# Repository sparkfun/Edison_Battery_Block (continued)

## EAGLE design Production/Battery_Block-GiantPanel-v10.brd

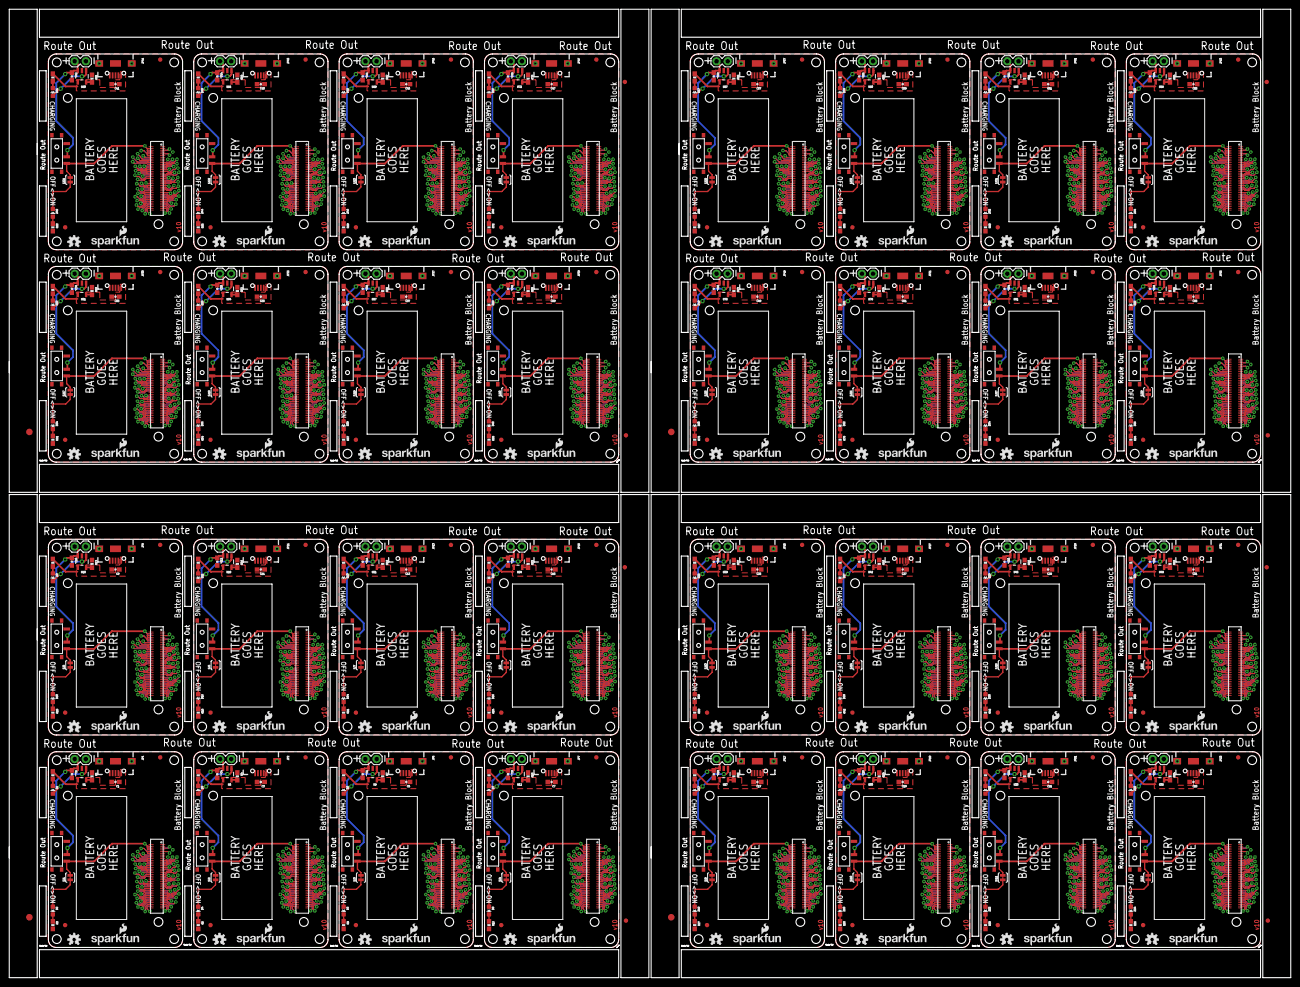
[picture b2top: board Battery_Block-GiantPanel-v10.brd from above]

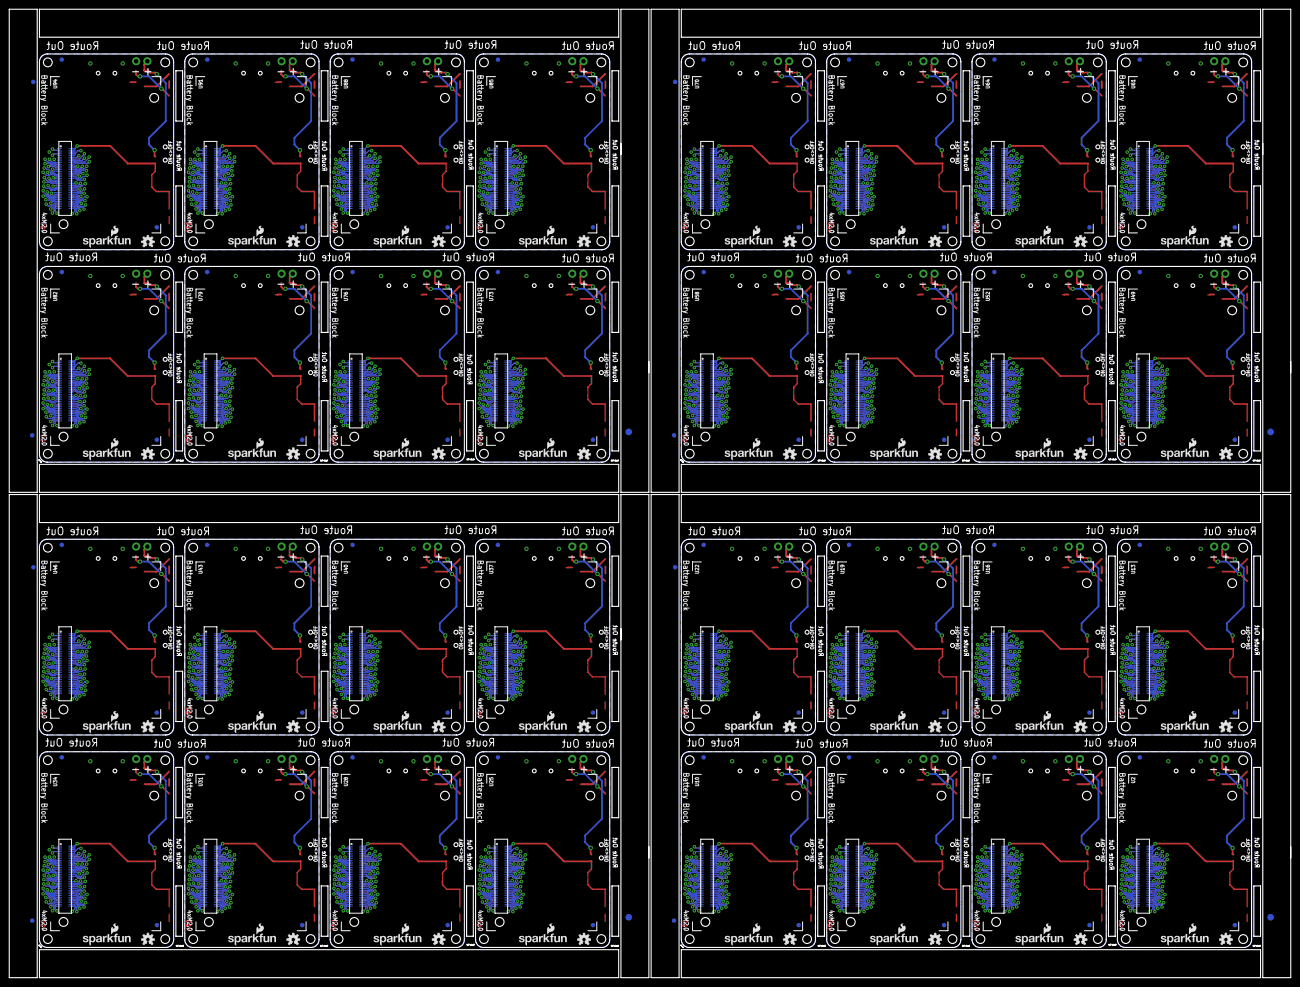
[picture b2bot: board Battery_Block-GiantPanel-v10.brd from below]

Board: 2 copper layers, 291.1 x 220.0 mm, 728 parts (204 on the bottom side), 2080 nets.

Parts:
C1, C2, C3, C4, C5, C6, C7, C8, C9, C10, C11, C12, C13, C14, C15, C16, C17, C18, C19, C20, C21, C22, C23, C24, C25, C26, C27, C28, C29, C30, C31, C32, C33, C34, C35, C36, C37, C38, C39, C40, C41, C42, C43, C44, C45, C46, C47, C48, C49, C50, C51, C52, C53, C54, C55, C56, C57, C58, C59, C60, C61, C62, C63, C64: 4.7uF; 0603-CAP
D1, D3, D5, D7, D9, D11, D13, D15, D17, D19, D21, D23, D25, D27, D29, D31, D33, D35, D37, D39, D41, D43, D45, D47, D49, D51, D53, D55, D57, D59, D61, D63: RED; LED-0603
D2, D4, D6, D8, D10, D12, D14, D16, D18, D20, D22, D24, D26, D28, D30, D32, D34, D36, D38, D40, D42, D44, D46, D48, D50, D52, D54, D56, D58, D60, D62, D64: BLUE; LED-0603
E$1, E$2, E$9, E$10, E$15, E$16, E$21, E$22: FIDUCIAL-1.5X3
E$3, E$4, E$5, E$6, E$7, E$8, E$11, E$12, E$13, E$14, E$17, E$18, E$19, E$20, E$23, E$24: FIDUCIAL-1X2
FID1, FID2, FID3, FID4, FID5, FID6, FID7, FID8, FID9, FID10, FID11, FID12, FID13, FID14, FID15, FID16, FID17, FID18, FID19, FID20, FID21, FID22, FID23, FID24, FID25, FID26, FID27, FID28, FID29, FID30, FID31, FID32, FID33, FID34, FID35, FID36, FID37, FID38, FID39, FID40, FID41, FID42, FID43, FID44, FID45, FID46, FID47, FID48, FID49, FID50, FID51, FID52, FID53, FID54, FID55, FID56, FID57, FID58, FID59, FID60, FID61, FID62, FID63, FID64, FID65, FID66, FID67, FID68, FID69, FID70, FID71, FID72, FID73, FID74, FID75, FID76, FID77, FID78, FID79, FID80, FID81, FID82, FID83, FID84, FID85, FID86, FID87, FID88, FID89, FID90, FID91, FID92, FID93, FID94, FID95, FID96, FID97, FID98, FID99, FID100, FID101, FID102, FID103, FID104, FID105, FID106, FID107, FID108, FID109, FID110, FID111, FID112, FID113, FID114, FID115, FID116, FID117, FID118, FID119, FID120, FID121, FID122, FID123, FID124, FID125, FID126, FID127, FID128: FIDUCIAL1X2; FIDUCIAL-1X2
JP1, JP2, JP5, JP7, JP9, JP11, JP13, JP15, JP17, JP19, JP21, JP23, JP25, JP27, JP29, JP31, JP33, JP35, JP37, JP39, JP41, JP43, JP45, JP47, JP49, JP51, JP53, JP55, JP57, JP59, JP61, JP63: USB_MICROB_PLUG; USB-B-MICRO-SMD_V03
JP3, JP4, JP6, JP8, JP10, JP12, JP14, JP16, JP18, JP20, JP22, JP24, JP26, JP28, JP30, JP32, JP34, JP36, JP38, JP40, JP42, JP44, JP46, JP48, JP50, JP52, JP54, JP56, JP58, JP60, JP62, JP64: M02PTH; 1X02
LOGO1, LOGO2, LOGO5, LOGO7, LOGO9, LOGO11, LOGO13, LOGO15, LOGO17, LOGO19, LOGO21, LOGO23, LOGO25, LOGO27, LOGO29, LOGO31, LOGO33, LOGO35, LOGO37, LOGO39, LOGO41, LOGO43, LOGO45, LOGO47, LOGO49, LOGO51, LOGO53, LOGO55, LOGO57, LOGO59, LOGO61, LOGO63, LOGO65, LOGO67, LOGO69, LOGO71, LOGO73, LOGO75, LOGO77, LOGO79, LOGO81, LOGO83, LOGO85, LOGO87, LOGO89, LOGO91, LOGO93, LOGO95, LOGO97, LOGO99, LOGO101, LOGO103, LOGO105, LOGO107, LOGO109, LOGO111, LOGO113, LOGO115, LOGO117, LOGO119, LOGO121, LOGO123, LOGO125, LOGO127: OSHW-LOGOS; OSHW-LOGO-S
LOGO3, LOGO4, LOGO6, LOGO8, LOGO10, LOGO12, LOGO14, LOGO16, LOGO18, LOGO20, LOGO22, LOGO24, LOGO26, LOGO28, LOGO30, LOGO32, LOGO34, LOGO36, LOGO38, LOGO40, LOGO42, LOGO44, LOGO46, LOGO48, LOGO50, LOGO52, LOGO54, LOGO56, LOGO58, LOGO60, LOGO62, LOGO64, LOGO66, LOGO68, LOGO70, LOGO72, LOGO74, LOGO76, LOGO78, LOGO80, LOGO82, LOGO84, LOGO86, LOGO88, LOGO90, LOGO92, LOGO94, LOGO96, LOGO98, LOGO100, LOGO102, LOGO104, LOGO106, LOGO108, LOGO110, LOGO112, LOGO114, LOGO116, LOGO118, LOGO120, LOGO122, LOGO124, LOGO126, LOGO128: SFE_LOGO_NAME_FLAME.1_INCH; SFE_LOGO_NAME_FLAME_.1
R1, R4, R7, R10, R13, R16, R19, R22, R25, R28, R31, R34, R37, R40, R43, R46, R49, R52, R55, R58, R61, R64, R67, R70, R73, R76, R79, R82, R85, R88, R91, R94: 2.0k; 0603-RES
R2, R5, R8, R11, R14, R17, R20, R23, R26, R29, R32, R35, R38, R41, R44, R47, R50, R53, R56, R59, R62, R65, R68, R71, R74, R77, R80, R83, R86, R89, R92, R95: 330; 0603-RES
R3, R6, R9, R12, R15, R18, R21, R24, R27, R30, R33, R36, R39, R42, R45, R48, R51, R54, R57, R60, R63, R66, R69, R72, R75, R78, R81, R84, R87, R90, R93, R96: 1k; 0603-RES
SJ1, SJ2, SJ3, SJ4, SJ5, SJ6, SJ7, SJ8, SJ9, SJ10, SJ11, SJ12, SJ13, SJ14, SJ15, SJ16, SJ17, SJ18, SJ19, SJ20, SJ21, SJ22, SJ23, SJ24, SJ25, SJ26, SJ27, SJ28, SJ29, SJ30, SJ31, SJ32: LED DISABLE; PAD-JUMPER-2-NC_BY_TRACE_YES_SILK
SW1, SW2, SW3, SW4, SW5, SW6, SW7, SW8, SW9, SW10, SW11, SW12, SW13, SW14, SW15, SW16, SW17, SW18, SW19, SW20, SW21, SW22, SW23, SW24, SW25, SW26, SW27, SW28, SW29, SW30, SW31, SW32: SWITCH_SPDT; KPS-1290
U1, U6, U9, U12, U15, U18, U21, U24, U27, U30, U33, U36, U39, U42, U45, U48, U51, U54, U57, U60, U63, U66, U69, U72, U75, U78, U81, U84, U87, U90, U93, U96: MCP73831; SOT23-5
U2, U4, U7, U10, U13, U16, U19, U22, U25, U28, U31, U34, U37, U40, U43, U46, U49, U52, U55, U58, U61, U64, U67, U70, U73, U76, U79, U82, U85, U88, U91, U94: EDISON_CONNECTOR_FULLMOUNTING_HOLES; EDISON_DAUGHTER
U3, U5, U8, U11, U14, U17, U20, U23, U26, U29, U32, U35, U38, U41, U44, U47, U50, U53, U56, U59, U62, U65, U68, U71, U74, U77, U80, U83, U86, U89, U92, U95: EDISON_CONNECTOR_FULLHEADER; DF40C-70DP-0.4(51)

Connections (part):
1.8V: U2.12, U3.12
1.8V1: U4.12, U5.12
1.8V2: U7.12, U8.12
1.8V3: U10.12, U11.12
1.8V4: U13.12, U14.12
1.8V5: U16.12, U17.12
1.8V6: U19.12, U20.12
1.8V7: U22.12, U23.12
1.8V8: U25.12, U26.12
1.8V9: U28.12, U29.12
1.8V10: U31.12, U32.12
1.8V11: U34.12, U35.12
1.8V12: U37.12, U38.12
1.8V13: U40.12, U41.12
1.8V14: U43.12, U44.12
1.8V15: U46.12, U47.12
1.8V16: U49.12, U50.12
1.8V17: U52.12, U53.12
1.8V18: U55.12, U56.12
1.8V19: U58.12, U59.12
1.8V20: U61.12, U62.12
1.8V21: U64.12, U65.12
1.8V22: U67.12, U68.12
1.8V23: U70.12, U71.12
1.8V24: U73.12, U74.12
1.8V25: U76.12, U77.12
1.8V26: U79.12, U80.12
1.8V27: U82.12, U83.12
1.8V28: U85.12, U86.12
1.8V29: U88.12, U89.12
1.8V30: U91.12, U92.12
1.8V31: U94.12, U95.12
3.3V: U2.8, U2.10, U3.8, U3.10
3.3V1: U4.8, U4.10, U5.8, U5.10
3.3V2: U7.8, U7.10, U8.8, U8.10
3.3V3: U10.8, U10.10, U11.8, U11.10
3.3V4: U13.8, U13.10, U14.8, U14.10
3.3V5: U16.8, U16.10, U17.8, U17.10
3.3V6: U19.8, U19.10, U20.8, U20.10
3.3V7: U22.8, U22.10, U23.8, U23.10
3.3V8: U25.8, U25.10, U26.8, U26.10
3.3V9: U28.8, U28.10, U29.8, U29.10
3.3V10: U31.8, U31.10, U32.8, U32.10
3.3V11: U34.8, U34.10, U35.8, U35.10
3.3V12: U37.8, U37.10, U38.8, U38.10
3.3V13: U40.8, U40.10, U41.8, U41.10
3.3V14: U43.8, U43.10, U44.8, U44.10
3.3V15: U46.8, U46.10, U47.8, U47.10
3.3V16: U49.8, U49.10, U50.8, U50.10
3.3V17: U52.8, U52.10, U53.8, U53.10
3.3V18: U55.8, U55.10, U56.8, U56.10
3.3V19: U58.8, U58.10, U59.8, U59.10
3.3V20: U61.8, U61.10, U62.8, U62.10
3.3V21: U64.8, U64.10, U65.8, U65.10
3.3V22: U67.8, U67.10, U68.8, U68.10
3.3V23: U70.8, U70.10, U71.8, U71.10
3.3V24: U73.8, U73.10, U74.8, U74.10
3.3V25: U76.8, U76.10, U77.8, U77.10
3.3V26: U79.8, U79.10, U80.8, U80.10
3.3V27: U82.8, U82.10, U83.8, U83.10
3.3V28: U85.8, U85.10, U86.8, U86.10
3.3V29: U88.8, U88.10, U89.8, U89.10
3.3V30: U91.8, U91.10, U92.8, U92.10
3.3V31: U94.8, U94.10, U95.8, U95.10
DCIN: U2.14, U3.14
DCIN1: U4.14, U5.14
DCIN2: U7.14, U8.14
DCIN3: U10.14, U11.14
DCIN4: U13.14, U14.14
DCIN5: U16.14, U17.14
DCIN6: U19.14, U20.14
DCIN7: U22.14, U23.14
DCIN8: U25.14, U26.14
DCIN9: U28.14, U29.14
DCIN10: U31.14, U32.14
DCIN11: U34.14, U35.14
DCIN12: U37.14, U38.14
DCIN13: U40.14, U41.14
DCIN14: U43.14, U44.14
DCIN15: U46.14, U47.14
DCIN16: U49.14, U50.14
DCIN17: U52.14, U53.14
DCIN18: U55.14, U56.14
DCIN19: U58.14, U59.14
DCIN20: U61.14, U62.14
DCIN21: U64.14, U65.14
DCIN22: U67.14, U68.14
DCIN23: U70.14, U71.14
DCIN24: U73.14, U74.14
DCIN25: U76.14, U77.14
DCIN26: U79.14, U80.14
DCIN27: U82.14, U83.14
DCIN28: U85.14, U86.14
DCIN29: U88.14, U89.14
DCIN30: U91.14, U92.14
DCIN31: U94.14, U95.14
FAULT: U2.19, U3.19
FAULT1: U4.19, U5.19
FAULT2: U7.19, U8.19
FAULT3: U10.19, U11.19
FAULT4: U13.19, U14.19
FAULT5: U16.19, U17.19
FAULT6: U19.19, U20.19
FAULT7: U22.19, U23.19
FAULT8: U25.19, U26.19
FAULT9: U28.19, U29.19
FAULT10: U31.19, U32.19
FAULT11: U34.19, U35.19
FAULT12: U37.19, U38.19
FAULT13: U40.19, U41.19
FAULT14: U43.19, U44.19
FAULT15: U46.19, U47.19
FAULT16: U49.19, U50.19
FAULT17: U52.19, U53.19
FAULT18: U55.19, U56.19
FAULT19: U58.19, U59.19
FAULT20: U61.19, U62.19
FAULT21: U64.19, U65.19
FAULT22: U67.19, U68.19
FAULT23: U70.19, U71.19
FAULT24: U73.19, U74.19
FAULT25: U76.19, U77.19
FAULT26: U79.19, U80.19
FAULT27: U82.19, U83.19
FAULT28: U85.19, U86.19
FAULT29: U88.19, U89.19
FAULT30: U91.19, U92.19
FAULT31: U94.19, U95.19
FW_RCVR: U2.69, U3.69
FW_RCVR1: U4.69, U5.69
FW_RCVR2: U7.69, U8.69
FW_RCVR3: U10.69, U11.69
FW_RCVR4: U13.69, U14.69
FW_RCVR5: U16.69, U17.69
FW_RCVR6: U19.69, U20.69
FW_RCVR7: U22.69, U23.69
FW_RCVR8: U25.69, U26.69
FW_RCVR9: U28.69, U29.69
FW_RCVR10: U31.69, U32.69
FW_RCVR11: U34.69, U35.69
FW_RCVR12: U37.69, U38.69
FW_RCVR13: U40.69, U41.69
FW_RCVR14: U43.69, U44.69
FW_RCVR15: U46.69, U47.69
FW_RCVR16: U49.69, U50.69
FW_RCVR17: U52.69, U53.69
FW_RCVR18: U55.69, U56.69
FW_RCVR19: U58.69, U59.69
FW_RCVR20: U61.69, U62.69
FW_RCVR21: U64.69, U65.69
FW_RCVR22: U67.69, U68.69
FW_RCVR23: U70.69, U71.69
FW_RCVR24: U73.69, U74.69
FW_RCVR25: U76.69, U77.69
FW_RCVR26: U79.69, U80.69
FW_RCVR27: U82.69, U83.69
FW_RCVR28: U85.69, U86.69
FW_RCVR29: U88.69, U89.69
FW_RCVR30: U91.69, U92.69
FW_RCVR31: U94.69, U95.69
GND: C1.2, C2.2, JP1.GND1, JP1.SHIELD1, JP1.SHIELD2, JP1.SHIELD3, JP3.2, R1.1, R3.2, U1.2, U2.1, U2.5, U2.9, U2.11, U2.13, U2.15, U3.1, U3.5, U3.9, U3.11, U3.13, U3.15
GND1: C3.2, C4.2, JP2.GND1, JP2.SHIELD1, JP2.SHIELD2, JP2.SHIELD3, JP4.2, R4.1, R6.2, U4.1, U4.5, U4.9, U4.11, U4.13, U4.15, U5.1, U5.5, U5.9, U5.11, U5.13, U5.15, U6.2
GND2: C5.2, C6.2, JP5.GND1, JP5.SHIELD1, JP5.SHIELD2, JP5.SHIELD3, JP6.2, R7.1, R9.2, U7.1, U7.5, U7.9, U7.11, U7.13, U7.15, U8.1, U8.5, U8.9, U8.11, U8.13, U8.15, U9.2
GND3: C7.2, C8.2, JP7.GND1, JP7.SHIELD1, JP7.SHIELD2, JP7.SHIELD3, JP8.2, R10.1, R12.2, U10.1, U10.5, U10.9, U10.11, U10.13, U10.15, U11.1, U11.5, U11.9, U11.11, U11.13, U11.15, U12.2
GND4: C9.2, C10.2, JP9.GND1, JP9.SHIELD1, JP9.SHIELD2, JP9.SHIELD3, JP10.2, R13.1, R15.2, U13.1, U13.5, U13.9, U13.11, U13.13, U13.15, U14.1, U14.5, U14.9, U14.11, U14.13, U14.15, U15.2
GND5: C11.2, C12.2, JP11.GND1, JP11.SHIELD1, JP11.SHIELD2, JP11.SHIELD3, JP12.2, R16.1, R18.2, U16.1, U16.5, U16.9, U16.11, U16.13, U16.15, U17.1, U17.5, U17.9, U17.11, U17.13, U17.15, U18.2
GND6: C13.2, C14.2, JP13.GND1, JP13.SHIELD1, JP13.SHIELD2, JP13.SHIELD3, JP14.2, R19.1, R21.2, U19.1, U19.5, U19.9, U19.11, U19.13, U19.15, U20.1, U20.5, U20.9, U20.11, U20.13, U20.15, U21.2
GND7: C15.2, C16.2, JP15.GND1, JP15.SHIELD1, JP15.SHIELD2, JP15.SHIELD3, JP16.2, R22.1, R24.2, U22.1, U22.5, U22.9, U22.11, U22.13, U22.15, U23.1, U23.5, U23.9, U23.11, U23.13, U23.15, U24.2
GND8: C17.2, C18.2, JP17.GND1, JP17.SHIELD1, JP17.SHIELD2, JP17.SHIELD3, JP18.2, R25.1, R27.2, U25.1, U25.5, U25.9, U25.11, U25.13, U25.15, U26.1, U26.5, U26.9, U26.11, U26.13, U26.15, U27.2
GND9: C19.2, C20.2, JP19.GND1, JP19.SHIELD1, JP19.SHIELD2, JP19.SHIELD3, JP20.2, R28.1, R30.2, U28.1, U28.5, U28.9, U28.11, U28.13, U28.15, U29.1, U29.5, U29.9, U29.11, U29.13, U29.15, U30.2
GND10: C21.2, C22.2, JP21.GND1, JP21.SHIELD1, JP21.SHIELD2, JP21.SHIELD3, JP22.2, R31.1, R33.2, U31.1, U31.5, U31.9, U31.11, U31.13, U31.15, U32.1, U32.5, U32.9, U32.11, U32.13, U32.15, U33.2
GND11: C23.2, C24.2, JP23.GND1, JP23.SHIELD1, JP23.SHIELD2, JP23.SHIELD3, JP24.2, R34.1, R36.2, U34.1, U34.5, U34.9, U34.11, U34.13, U34.15, U35.1, U35.5, U35.9, U35.11, U35.13, U35.15, U36.2
GND12: C25.2, C26.2, JP25.GND1, JP25.SHIELD1, JP25.SHIELD2, JP25.SHIELD3, JP26.2, R37.1, R39.2, U37.1, U37.5, U37.9, U37.11, U37.13, U37.15, U38.1, U38.5, U38.9, U38.11, U38.13, U38.15, U39.2
GND13: C27.2, C28.2, JP27.GND1, JP27.SHIELD1, JP27.SHIELD2, JP27.SHIELD3, JP28.2, R40.1, R42.2, U40.1, U40.5, U40.9, U40.11, U40.13, U40.15, U41.1, U41.5, U41.9, U41.11, U41.13, U41.15, U42.2
GND14: C29.2, C30.2, JP29.GND1, JP29.SHIELD1, JP29.SHIELD2, JP29.SHIELD3, JP30.2, R43.1, R45.2, U43.1, U43.5, U43.9, U43.11, U43.13, U43.15, U44.1, U44.5, U44.9, U44.11, U44.13, U44.15, U45.2
GND15: C31.2, C32.2, JP31.GND1, JP31.SHIELD1, JP31.SHIELD2, JP31.SHIELD3, JP32.2, R46.1, R48.2, U46.1, U46.5, U46.9, U46.11, U46.13, U46.15, U47.1, U47.5, U47.9, U47.11, U47.13, U47.15, U48.2
GND16: C33.2, C34.2, JP33.GND1, JP33.SHIELD1, JP33.SHIELD2, JP33.SHIELD3, JP34.2, R49.1, R51.2, U49.1, U49.5, U49.9, U49.11, U49.13, U49.15, U50.1, U50.5, U50.9, U50.11, U50.13, U50.15, U51.2
GND17: C35.2, C36.2, JP35.GND1, JP35.SHIELD1, JP35.SHIELD2, JP35.SHIELD3, JP36.2, R52.1, R54.2, U52.1, U52.5, U52.9, U52.11, U52.13, U52.15, U53.1, U53.5, U53.9, U53.11, U53.13, U53.15, U54.2
GND18: C37.2, C38.2, JP37.GND1, JP37.SHIELD1, JP37.SHIELD2, JP37.SHIELD3, JP38.2, R55.1, R57.2, U55.1, U55.5, U55.9, U55.11, U55.13, U55.15, U56.1, U56.5, U56.9, U56.11, U56.13, U56.15, U57.2
GND19: C39.2, C40.2, JP39.GND1, JP39.SHIELD1, JP39.SHIELD2, JP39.SHIELD3, JP40.2, R58.1, R60.2, U58.1, U58.5, U58.9, U58.11, U58.13, U58.15, U59.1, U59.5, U59.9, U59.11, U59.13, U59.15, U60.2
GND20: C41.2, C42.2, JP41.GND1, JP41.SHIELD1, JP41.SHIELD2, JP41.SHIELD3, JP42.2, R61.1, R63.2, U61.1, U61.5, U61.9, U61.11, U61.13, U61.15, U62.1, U62.5, U62.9, U62.11, U62.13, U62.15, U63.2
GND21: C43.2, C44.2, JP43.GND1, JP43.SHIELD1, JP43.SHIELD2, JP43.SHIELD3, JP44.2, R64.1, R66.2, U64.1, U64.5, U64.9, U64.11, U64.13, U64.15, U65.1, U65.5, U65.9, U65.11, U65.13, U65.15, U66.2
GND22: C45.2, C46.2, JP45.GND1, JP45.SHIELD1, JP45.SHIELD2, JP45.SHIELD3, JP46.2, R67.1, R69.2, U67.1, U67.5, U67.9, U67.11, U67.13, U67.15, U68.1, U68.5, U68.9, U68.11, U68.13, U68.15, U69.2
GND23: C47.2, C48.2, JP47.GND1, JP47.SHIELD1, JP47.SHIELD2, JP47.SHIELD3, JP48.2, R70.1, R72.2, U70.1, U70.5, U70.9, U70.11, U70.13, U70.15, U71.1, U71.5, U71.9, U71.11, U71.13, U71.15, U72.2
GND24: C49.2, C50.2, JP49.GND1, JP49.SHIELD1, JP49.SHIELD2, JP49.SHIELD3, JP50.2, R73.1, R75.2, U73.1, U73.5, U73.9, U73.11, U73.13, U73.15, U74.1, U74.5, U74.9, U74.11, U74.13, U74.15, U75.2
GND25: C51.2, C52.2, JP51.GND1, JP51.SHIELD1, JP51.SHIELD2, JP51.SHIELD3, JP52.2, R76.1, R78.2, U76.1, U76.5, U76.9, U76.11, U76.13, U76.15, U77.1, U77.5, U77.9, U77.11, U77.13, U77.15, U78.2
GND26: C53.2, C54.2, JP53.GND1, JP53.SHIELD1, JP53.SHIELD2, JP53.SHIELD3, JP54.2, R79.1, R81.2, U79.1, U79.5, U79.9, U79.11, U79.13, U79.15, U80.1, U80.5, U80.9, U80.11, U80.13, U80.15, U81.2
GND27: C55.2, C56.2, JP55.GND1, JP55.SHIELD1, JP55.SHIELD2, JP55.SHIELD3, JP56.2, R82.1, R84.2, U82.1, U82.5, U82.9, U82.11, U82.13, U82.15, U83.1, U83.5, U83.9, U83.11, U83.13, U83.15, U84.2
GND28: C57.2, C58.2, JP57.GND1, JP57.SHIELD1, JP57.SHIELD2, JP57.SHIELD3, JP58.2, R85.1, R87.2, U85.1, U85.5, U85.9, U85.11, U85.13, U85.15, U86.1, U86.5, U86.9, U86.11, U86.13, U86.15, U87.2
GND29: C59.2, C60.2, JP59.GND1, JP59.SHIELD1, JP59.SHIELD2, JP59.SHIELD3, JP60.2, R88.1, R90.2, U88.1, U88.5, U88.9, U88.11, U88.13, U88.15, U89.1, U89.5, U89.9, U89.11, U89.13, U89.15, U90.2
GND30: C61.2, C62.2, JP61.GND1, JP61.SHIELD1, JP61.SHIELD2, JP61.SHIELD3, JP62.2, R91.1, R93.2, U91.1, U91.5, U91.9, U91.11, U91.13, U91.15, U92.1, U92.5, U92.9, U92.11, U92.13, U92.15, U93.2
GND31: C63.2, C64.2, JP63.GND1, JP63.SHIELD1, JP63.SHIELD2, JP63.SHIELD3, JP64.2, R94.1, R96.2, U94.1, U94.5, U94.9, U94.11, U94.13, U94.15, U95.1, U95.5, U95.9, U95.11, U95.13, U95.15, U96.2
GP1: U4.48, U5.48
GP2: U4.42, U5.42
GP3: U4.34, U5.34
GP4: U4.32, U5.32
GP5: U4.30, U5.30
GP6: U4.28, U5.28
GP7: U4.26, U5.26
GP8: U4.25, U5.25
GP9: U4.24, U5.24
GP10: U7.48, U8.48
GP11: U7.42, U8.42
GP12: U7.34, U8.34
GP12_PWM0: U2.35, U3.35
GP12_PWM1: U4.35, U5.35
GP12_PWM2: U7.35, U8.35
GP12_PWM3: U10.35, U11.35
GP12_PWM4: U13.35, U14.35
GP12_PWM5: U16.35, U17.35
GP12_PWM6: U19.35, U20.35
GP12_PWM7: U22.35, U23.35
GP12_PWM8: U25.35, U26.35
GP12_PWM9: U28.35, U29.35
GP12_PWM10: U31.35, U32.35
GP12_PWM11: U34.35, U35.35
GP12_PWM12: U37.35, U38.35
GP12_PWM13: U40.35, U41.35
GP12_PWM14: U43.35, U44.35
GP12_PWM15: U46.35, U47.35
GP12_PWM16: U49.35, U50.35
GP12_PWM17: U52.35, U53.35
GP12_PWM18: U55.35, U56.35
GP12_PWM19: U58.35, U59.35
GP12_PWM20: U61.35, U62.35
GP12_PWM21: U64.35, U65.35
GP12_PWM22: U67.35, U68.35
GP12_PWM23: U70.35, U71.35
GP12_PWM24: U73.35, U74.35
GP12_PWM25: U76.35, U77.35
GP12_PWM26: U79.35, U80.35
GP12_PWM27: U82.35, U83.35
GP12_PWM28: U85.35, U86.35
GP12_PWM29: U88.35, U89.35
GP12_PWM30: U91.35, U92.35
GP12_PWM31: U94.35, U95.35
GP13: U7.32, U8.32
GP13_PWM1: U2.33, U3.33
GP13_PWM2: U4.33, U5.33
GP13_PWM3: U7.33, U8.33
GP13_PWM4: U10.33, U11.33
GP13_PWM5: U13.33, U14.33
GP13_PWM6: U16.33, U17.33
GP13_PWM7: U19.33, U20.33
GP13_PWM8: U22.33, U23.33
GP13_PWM9: U25.33, U26.33
GP13_PWM10: U28.33, U29.33
GP13_PWM11: U31.33, U32.33
GP13_PWM12: U34.33, U35.33
GP13_PWM13: U37.33, U38.33
GP13_PWM14: U40.33, U41.33
GP13_PWM15: U43.33, U44.33
GP13_PWM16: U46.33, U47.33
GP13_PWM17: U49.33, U50.33
GP13_PWM18: U52.33, U53.33
GP13_PWM19: U55.33, U56.33
GP13_PWM20: U58.33, U59.33
GP13_PWM21: U61.33, U62.33
GP13_PWM22: U64.33, U65.33
GP13_PWM23: U67.33, U68.33
GP13_PWM24: U70.33, U71.33
GP13_PWM25: U73.33, U74.33
GP13_PWM26: U76.33, U77.33
GP13_PWM27: U79.33, U80.33
GP13_PWM28: U82.33, U83.33
GP13_PWM29: U85.33, U86.33
GP13_PWM30: U88.33, U89.33
GP13_PWM31: U91.33, U92.33
GP13_PWM32: U94.33, U95.33
GP14: U2.48, U3.48
GP15: U2.42, U3.42
GP16: U7.30, U8.30
GP17: U7.28, U8.28
GP18: U7.26, U8.26
GP19: U7.25, U8.25
GP19_I2C_1_SCL: U2.41, U3.41
GP19_I2C_1_SCL1: U4.41, U5.41
GP19_I2C_1_SCL2: U7.41, U8.41
GP19_I2C_1_SCL3: U10.41, U11.41
GP19_I2C_1_SCL4: U13.41, U14.41
GP19_I2C_1_SCL5: U16.41, U17.41
GP19_I2C_1_SCL6: U19.41, U20.41
GP19_I2C_1_SCL7: U22.41, U23.41
GP19_I2C_1_SCL8: U25.41, U26.41
GP19_I2C_1_SCL9: U28.41, U29.41
GP19_I2C_1_SCL10: U31.41, U32.41
GP19_I2C_1_SCL11: U34.41, U35.41
GP19_I2C_1_SCL12: U37.41, U38.41
GP19_I2C_1_SCL13: U40.41, U41.41
GP19_I2C_1_SCL14: U43.41, U44.41
GP19_I2C_1_SCL15: U46.41, U47.41
GP19_I2C_1_SCL16: U49.41, U50.41
GP19_I2C_1_SCL17: U52.41, U53.41
GP19_I2C_1_SCL18: U55.41, U56.41
GP19_I2C_1_SCL19: U58.41, U59.41
GP19_I2C_1_SCL20: U61.41, U62.41
GP19_I2C_1_SCL21: U64.41, U65.41
GP19_I2C_1_SCL22: U67.41, U68.41
GP19_I2C_1_SCL23: U70.41, U71.41
GP19_I2C_1_SCL24: U73.41, U74.41
GP19_I2C_1_SCL25: U76.41, U77.41
GP19_I2C_1_SCL26: U79.41, U80.41
GP19_I2C_1_SCL27: U82.41, U83.41
GP19_I2C_1_SCL28: U85.41, U86.41
GP19_I2C_1_SCL29: U88.41, U89.41
GP19_I2C_1_SCL30: U91.41, U92.41
GP19_I2C_1_SCL31: U94.41, U95.41
GP20: U7.24, U8.24
GP20_I2C_1_SDA: U2.43, U3.43
GP20_I2C_1_SDA1: U4.43, U5.43
GP20_I2C_1_SDA2: U7.43, U8.43
GP20_I2C_1_SDA3: U10.43, U11.43
GP20_I2C_1_SDA4: U13.43, U14.43
GP20_I2C_1_SDA5: U16.43, U17.43
GP20_I2C_1_SDA6: U19.43, U20.43
GP20_I2C_1_SDA7: U22.43, U23.43
GP20_I2C_1_SDA8: U25.43, U26.43
GP20_I2C_1_SDA9: U28.43, U29.43
GP20_I2C_1_SDA10: U31.43, U32.43
GP20_I2C_1_SDA11: U34.43, U35.43
GP20_I2C_1_SDA12: U37.43, U38.43
GP20_I2C_1_SDA13: U40.43, U41.43
GP20_I2C_1_SDA14: U43.43, U44.43
GP20_I2C_1_SDA15: U46.43, U47.43
GP20_I2C_1_SDA16: U49.43, U50.43
GP20_I2C_1_SDA17: U52.43, U53.43
GP20_I2C_1_SDA18: U55.43, U56.43
GP20_I2C_1_SDA19: U58.43, U59.43
GP20_I2C_1_SDA20: U61.43, U62.43
GP20_I2C_1_SDA21: U64.43, U65.43
GP20_I2C_1_SDA22: U67.43, U68.43
GP20_I2C_1_SDA23: U70.43, U71.43
GP20_I2C_1_SDA24: U73.43, U74.43
GP20_I2C_1_SDA25: U76.43, U77.43
GP20_I2C_1_SDA26: U79.43, U80.43
GP20_I2C_1_SDA27: U82.43, U83.43
GP20_I2C_1_SDA28: U85.43, U86.43
GP20_I2C_1_SDA29: U88.43, U89.43
GP20_I2C_1_SDA30: U91.43, U92.43
GP20_I2C_1_SDA31: U94.43, U95.43
GP21: U10.48, U11.48
GP22: U10.42, U11.42
GP23: U10.34, U11.34
GP24: U10.32, U11.32
GP25: U10.30, U11.30
GP26: U10.28, U11.28
GP27: U10.26, U11.26
GP27_I2C_6_SCL: U2.45, U3.45
GP27_I2C_6_SCL1: U4.45, U5.45
GP27_I2C_6_SCL2: U7.45, U8.45
GP27_I2C_6_SCL3: U10.45, U11.45
GP27_I2C_6_SCL4: U13.45, U14.45
GP27_I2C_6_SCL5: U16.45, U17.45
GP27_I2C_6_SCL6: U19.45, U20.45
GP27_I2C_6_SCL7: U22.45, U23.45
GP27_I2C_6_SCL8: U25.45, U26.45
GP27_I2C_6_SCL9: U28.45, U29.45
GP27_I2C_6_SCL10: U31.45, U32.45
GP27_I2C_6_SCL11: U34.45, U35.45
GP27_I2C_6_SCL12: U37.45, U38.45
GP27_I2C_6_SCL13: U40.45, U41.45
GP27_I2C_6_SCL14: U43.45, U44.45
GP27_I2C_6_SCL15: U46.45, U47.45
GP27_I2C_6_SCL16: U49.45, U50.45
GP27_I2C_6_SCL17: U52.45, U53.45
GP27_I2C_6_SCL18: U55.45, U56.45
GP27_I2C_6_SCL19: U58.45, U59.45
GP27_I2C_6_SCL20: U61.45, U62.45
GP27_I2C_6_SCL21: U64.45, U65.45
GP27_I2C_6_SCL22: U67.45, U68.45
GP27_I2C_6_SCL23: U70.45, U71.45
GP27_I2C_6_SCL24: U73.45, U74.45
GP27_I2C_6_SCL25: U76.45, U77.45
GP27_I2C_6_SCL26: U79.45, U80.45
GP27_I2C_6_SCL27: U82.45, U83.45
GP27_I2C_6_SCL28: U85.45, U86.45
GP27_I2C_6_SCL29: U88.45, U89.45
GP27_I2C_6_SCL30: U91.45, U92.45
GP27_I2C_6_SCL31: U94.45, U95.45
GP28: U10.25, U11.25
GP28_I2C_6_SDA: U2.47, U3.47
GP28_I2C_6_SDA1: U4.47, U5.47
GP28_I2C_6_SDA2: U7.47, U8.47
GP28_I2C_6_SDA3: U10.47, U11.47
GP28_I2C_6_SDA4: U13.47, U14.47
GP28_I2C_6_SDA5: U16.47, U17.47
GP28_I2C_6_SDA6: U19.47, U20.47
GP28_I2C_6_SDA7: U22.47, U23.47
GP28_I2C_6_SDA8: U25.47, U26.47
GP28_I2C_6_SDA9: U28.47, U29.47
GP28_I2C_6_SDA10: U31.47, U32.47
GP28_I2C_6_SDA11: U34.47, U35.47
GP28_I2C_6_SDA12: U37.47, U38.47
GP28_I2C_6_SDA13: U40.47, U41.47
GP28_I2C_6_SDA14: U43.47, U44.47
GP28_I2C_6_SDA15: U46.47, U47.47
GP28_I2C_6_SDA16: U49.47, U50.47
GP28_I2C_6_SDA17: U52.47, U53.47
GP28_I2C_6_SDA18: U55.47, U56.47
GP28_I2C_6_SDA19: U58.47, U59.47
GP28_I2C_6_SDA20: U61.47, U62.47
GP28_I2C_6_SDA21: U64.47, U65.47
GP28_I2C_6_SDA22: U67.47, U68.47
GP28_I2C_6_SDA23: U70.47, U71.47
GP28_I2C_6_SDA24: U73.47, U74.47
GP28_I2C_6_SDA25: U76.47, U77.47
GP28_I2C_6_SDA26: U79.47, U80.47
GP28_I2C_6_SDA27: U82.47, U83.47
GP28_I2C_6_SDA28: U85.47, U86.47
GP28_I2C_6_SDA29: U88.47, U89.47
GP28_I2C_6_SDA30: U91.47, U92.47
GP28_I2C_6_SDA31: U94.47, U95.47
GP29: U10.24, U11.24
GP30: U13.48, U14.48
GP31: U13.42, U14.42
GP32: U13.34, U14.34
GP33: U13.32, U14.32
GP34: U13.30, U14.30
GP35: U13.28, U14.28
GP36: U13.26, U14.26
GP37: U13.25, U14.25
GP38: U13.24, U14.24
GP39: U16.48, U17.48
GP40: U16.42, U17.42
GP40_I2S_2_CLK: U2.52, U3.52
GP40_I2S_2_CLK1: U4.52, U5.52
GP40_I2S_2_CLK2: U7.52, U8.52
GP40_I2S_2_CLK3: U10.52, U11.52
GP40_I2S_2_CLK4: U13.52, U14.52
GP40_I2S_2_CLK5: U16.52, U17.52
GP40_I2S_2_CLK6: U19.52, U20.52
GP40_I2S_2_CLK7: U22.52, U23.52
GP40_I2S_2_CLK8: U25.52, U26.52
GP40_I2S_2_CLK9: U28.52, U29.52
GP40_I2S_2_CLK10: U31.52, U32.52
GP40_I2S_2_CLK11: U34.52, U35.52
GP40_I2S_2_CLK12: U37.52, U38.52
GP40_I2S_2_CLK13: U40.52, U41.52
GP40_I2S_2_CLK14: U43.52, U44.52
GP40_I2S_2_CLK15: U46.52, U47.52
GP40_I2S_2_CLK16: U49.52, U50.52
GP40_I2S_2_CLK17: U52.52, U53.52
GP40_I2S_2_CLK18: U55.52, U56.52
GP40_I2S_2_CLK19: U58.52, U59.52
GP40_I2S_2_CLK20: U61.52, U62.52
GP40_I2S_2_CLK21: U64.52, U65.52
GP40_I2S_2_CLK22: U67.52, U68.52
GP40_I2S_2_CLK23: U70.52, U71.52
GP40_I2S_2_CLK24: U73.52, U74.52
GP40_I2S_2_CLK25: U76.52, U77.52
GP40_I2S_2_CLK26: U79.52, U80.52
GP40_I2S_2_CLK27: U82.52, U83.52
GP40_I2S_2_CLK28: U85.52, U86.52
GP40_I2S_2_CLK29: U88.52, U89.52
GP40_I2S_2_CLK30: U91.52, U92.52
GP40_I2S_2_CLK31: U94.52, U95.52
GP41: U16.34, U17.34
GP41_I2S_2_FS: U2.54, U3.54
GP41_I2S_2_FS1: U4.54, U5.54
GP41_I2S_2_FS2: U7.54, U8.54
GP41_I2S_2_FS3: U10.54, U11.54
GP41_I2S_2_FS4: U13.54, U14.54
GP41_I2S_2_FS5: U16.54, U17.54
GP41_I2S_2_FS6: U19.54, U20.54
GP41_I2S_2_FS7: U22.54, U23.54
GP41_I2S_2_FS8: U25.54, U26.54
GP41_I2S_2_FS9: U28.54, U29.54
GP41_I2S_2_FS10: U31.54, U32.54
GP41_I2S_2_FS11: U34.54, U35.54
GP41_I2S_2_FS12: U37.54, U38.54
GP41_I2S_2_FS13: U40.54, U41.54
GP41_I2S_2_FS14: U43.54, U44.54
GP41_I2S_2_FS15: U46.54, U47.54
GP41_I2S_2_FS16: U49.54, U50.54
GP41_I2S_2_FS17: U52.54, U53.54
GP41_I2S_2_FS18: U55.54, U56.54
GP41_I2S_2_FS19: U58.54, U59.54
GP41_I2S_2_FS20: U61.54, U62.54
GP41_I2S_2_FS21: U64.54, U65.54
GP41_I2S_2_FS22: U67.54, U68.54
GP41_I2S_2_FS23: U70.54, U71.54
GP41_I2S_2_FS24: U73.54, U74.54
GP41_I2S_2_FS25: U76.54, U77.54
GP41_I2S_2_FS26: U79.54, U80.54
GP41_I2S_2_FS27: U82.54, U83.54
GP41_I2S_2_FS28: U85.54, U86.54
GP41_I2S_2_FS29: U88.54, U89.54
GP41_I2S_2_FS30: U91.54, U92.54
GP41_I2S_2_FS31: U94.54, U95.54
GP42: U16.32, U17.32
GP42_I2S_2_RXD: U2.50, U3.50
GP42_I2S_2_RXD1: U4.50, U5.50
GP42_I2S_2_RXD2: U7.50, U8.50
GP42_I2S_2_RXD3: U10.50, U11.50
GP42_I2S_2_RXD4: U13.50, U14.50
GP42_I2S_2_RXD5: U16.50, U17.50
GP42_I2S_2_RXD6: U19.50, U20.50
GP42_I2S_2_RXD7: U22.50, U23.50
GP42_I2S_2_RXD8: U25.50, U26.50
GP42_I2S_2_RXD9: U28.50, U29.50
GP42_I2S_2_RXD10: U31.50, U32.50
GP42_I2S_2_RXD11: U34.50, U35.50
GP42_I2S_2_RXD12: U37.50, U38.50
GP42_I2S_2_RXD13: U40.50, U41.50
GP42_I2S_2_RXD14: U43.50, U44.50
GP42_I2S_2_RXD15: U46.50, U47.50
GP42_I2S_2_RXD16: U49.50, U50.50
GP42_I2S_2_RXD17: U52.50, U53.50
GP42_I2S_2_RXD18: U55.50, U56.50
GP42_I2S_2_RXD19: U58.50, U59.50
GP42_I2S_2_RXD20: U61.50, U62.50
GP42_I2S_2_RXD21: U64.50, U65.50
GP42_I2S_2_RXD22: U67.50, U68.50
GP42_I2S_2_RXD23: U70.50, U71.50
GP42_I2S_2_RXD24: U73.50, U74.50
GP42_I2S_2_RXD25: U76.50, U77.50
GP42_I2S_2_RXD26: U79.50, U80.50
GP42_I2S_2_RXD27: U82.50, U83.50
GP42_I2S_2_RXD28: U85.50, U86.50
GP42_I2S_2_RXD29: U88.50, U89.50
GP42_I2S_2_RXD30: U91.50, U92.50
GP42_I2S_2_RXD31: U94.50, U95.50
GP43: U16.30, U17.30
GP43_I2S_2_TXD: U2.56, U3.56
GP43_I2S_2_TXD1: U4.56, U5.56
GP43_I2S_2_TXD2: U7.56, U8.56
GP43_I2S_2_TXD3: U10.56, U11.56
GP43_I2S_2_TXD4: U13.56, U14.56
GP43_I2S_2_TXD5: U16.56, U17.56
GP43_I2S_2_TXD6: U19.56, U20.56
GP43_I2S_2_TXD7: U22.56, U23.56
GP43_I2S_2_TXD8: U25.56, U26.56
GP43_I2S_2_TXD9: U28.56, U29.56
GP43_I2S_2_TXD10: U31.56, U32.56
GP43_I2S_2_TXD11: U34.56, U35.56
GP43_I2S_2_TXD12: U37.56, U38.56
GP43_I2S_2_TXD13: U40.56, U41.56
GP43_I2S_2_TXD14: U43.56, U44.56
GP43_I2S_2_TXD15: U46.56, U47.56
GP43_I2S_2_TXD16: U49.56, U50.56
GP43_I2S_2_TXD17: U52.56, U53.56
GP43_I2S_2_TXD18: U55.56, U56.56
GP43_I2S_2_TXD19: U58.56, U59.56
GP43_I2S_2_TXD20: U61.56, U62.56
GP43_I2S_2_TXD21: U64.56, U65.56
GP43_I2S_2_TXD22: U67.56, U68.56
GP43_I2S_2_TXD23: U70.56, U71.56
GP43_I2S_2_TXD24: U73.56, U74.56
GP43_I2S_2_TXD25: U76.56, U77.56
GP43_I2S_2_TXD26: U79.56, U80.56
GP43_I2S_2_TXD27: U82.56, U83.56
GP43_I2S_2_TXD28: U85.56, U86.56
GP43_I2S_2_TXD29: U88.56, U89.56
GP43_I2S_2_TXD30: U91.56, U92.56
GP43_I2S_2_TXD31: U94.56, U95.56
GP44: U2.24, U3.24
GP45: U2.26, U3.26
GP46: U2.28, U3.28
GP47: U2.30, U3.30
GP48: U2.32, U3.32
GP49: U2.34, U3.34
GP50: U16.28, U17.28
GP51: U16.26, U17.26
GP52: U16.25, U17.25
GP53: U16.24, U17.24
GP54: U19.48, U20.48
GP55: U19.42, U20.42
GP56: U19.34, U20.34
GP57: U19.32, U20.32
GP58: U19.30, U20.30
GP59: U19.28, U20.28
GP60: U19.26, U20.26
GP61: U19.25, U20.25
GP62: U19.24, U20.24
GP63: U22.48, U23.48
GP64: U22.42, U23.42
GP65: U22.34, U23.34
GP66: U22.32, U23.32
GP67: U22.30, U23.30
GP68: U22.28, U23.28
GP69: U22.26, U23.26
GP70: U22.25, U23.25
GP71: U22.24, U23.24
GP72: U25.48, U26.48
GP73: U25.42, U26.42
GP74: U25.34, U26.34
GP75: U25.32, U26.32
GP76: U25.30, U26.30
GP77: U25.28, U26.28
GP77_SD_0_CD#: U2.60, U3.60
GP77_SD_0_CD#1: U4.60, U5.60
GP77_SD_0_CD#2: U7.60, U8.60
GP77_SD_0_CD#3: U10.60, U11.60
GP77_SD_0_CD#4: U13.60, U14.60
GP77_SD_0_CD#5: U16.60, U17.60
GP77_SD_0_CD#6: U19.60, U20.60
GP77_SD_0_CD#7: U22.60, U23.60
GP77_SD_0_CD#8: U25.60, U26.60
GP77_SD_0_CD#9: U28.60, U29.60
GP77_SD_0_CD#10: U31.60, U32.60
GP77_SD_0_CD#11: U34.60, U35.60
GP77_SD_0_CD#12: U37.60, U38.60
GP77_SD_0_CD#13: U40.60, U41.60
GP77_SD_0_CD#14: U43.60, U44.60
GP77_SD_0_CD#15: U46.60, U47.60
GP77_SD_0_CD#16: U49.60, U50.60
GP77_SD_0_CD#17: U52.60, U53.60
GP77_SD_0_CD#18: U55.60, U56.60
GP77_SD_0_CD#19: U58.60, U59.60
GP77_SD_0_CD#20: U61.60, U62.60
GP77_SD_0_CD#21: U64.60, U65.60
GP77_SD_0_CD#22: U67.60, U68.60
GP77_SD_0_CD#23: U70.60, U71.60
GP77_SD_0_CD#24: U73.60, U74.60
GP77_SD_0_CD#25: U76.60, U77.60
GP77_SD_0_CD#26: U79.60, U80.60
GP77_SD_0_CD#27: U82.60, U83.60
GP77_SD_0_CD#28: U85.60, U86.60
GP77_SD_0_CD#29: U88.60, U89.60
GP77_SD_0_CD#30: U91.60, U92.60
GP77_SD_0_CD#31: U94.60, U95.60
GP78: U25.26, U26.26
GP78_SD_0_CLK: U2.58, U3.58
GP78_SD_0_CLK1: U4.58, U5.58
GP78_SD_0_CLK2: U7.58, U8.58
GP78_SD_0_CLK3: U10.58, U11.58
GP78_SD_0_CLK4: U13.58, U14.58
GP78_SD_0_CLK5: U16.58, U17.58
GP78_SD_0_CLK6: U19.58, U20.58
GP78_SD_0_CLK7: U22.58, U23.58
GP78_SD_0_CLK8: U25.58, U26.58
GP78_SD_0_CLK9: U28.58, U29.58
GP78_SD_0_CLK10: U31.58, U32.58
GP78_SD_0_CLK11: U34.58, U35.58
GP78_SD_0_CLK12: U37.58, U38.58
GP78_SD_0_CLK13: U40.58, U41.58
GP78_SD_0_CLK14: U43.58, U44.58
GP78_SD_0_CLK15: U46.58, U47.58
GP78_SD_0_CLK16: U49.58, U50.58
GP78_SD_0_CLK17: U52.58, U53.58
GP78_SD_0_CLK18: U55.58, U56.58
GP78_SD_0_CLK19: U58.58, U59.58
GP78_SD_0_CLK20: U61.58, U62.58
GP78_SD_0_CLK21: U64.58, U65.58
GP78_SD_0_CLK22: U67.58, U68.58
GP78_SD_0_CLK23: U70.58, U71.58
GP78_SD_0_CLK24: U73.58, U74.58
GP78_SD_0_CLK25: U76.58, U77.58
GP78_SD_0_CLK26: U79.58, U80.58
GP78_SD_0_CLK27: U82.58, U83.58
GP78_SD_0_CLK28: U85.58, U86.58
GP78_SD_0_CLK29: U88.58, U89.58
GP78_SD_0_CLK30: U91.58, U92.58
GP78_SD_0_CLK31: U94.58, U95.58
GP79: U25.25, U26.25
GP79_SD_0_CMD: U2.62, U3.62
GP79_SD_0_CMD1: U4.62, U5.62
GP79_SD_0_CMD2: U7.62, U8.62
GP79_SD_0_CMD3: U10.62, U11.62
GP79_SD_0_CMD4: U13.62, U14.62
GP79_SD_0_CMD5: U16.62, U17.62
GP79_SD_0_CMD6: U19.62, U20.62
GP79_SD_0_CMD7: U22.62, U23.62
GP79_SD_0_CMD8: U25.62, U26.62
GP79_SD_0_CMD9: U28.62, U29.62
GP79_SD_0_CMD10: U31.62, U32.62
GP79_SD_0_CMD11: U34.62, U35.62
GP79_SD_0_CMD12: U37.62, U38.62
GP79_SD_0_CMD13: U40.62, U41.62
GP79_SD_0_CMD14: U43.62, U44.62
GP79_SD_0_CMD15: U46.62, U47.62
GP79_SD_0_CMD16: U49.62, U50.62
GP79_SD_0_CMD17: U52.62, U53.62
GP79_SD_0_CMD18: U55.62, U56.62
GP79_SD_0_CMD19: U58.62, U59.62
GP79_SD_0_CMD20: U61.62, U62.62
GP79_SD_0_CMD21: U64.62, U65.62
GP79_SD_0_CMD22: U67.62, U68.62
GP79_SD_0_CMD23: U70.62, U71.62
GP79_SD_0_CMD24: U73.62, U74.62
GP79_SD_0_CMD25: U76.62, U77.62
GP79_SD_0_CMD26: U79.62, U80.62
GP79_SD_0_CMD27: U82.62, U83.62
GP79_SD_0_CMD28: U85.62, U86.62
GP79_SD_0_CMD29: U88.62, U89.62
GP79_SD_0_CMD30: U91.62, U92.62
GP79_SD_0_CMD31: U94.62, U95.62
GP80: U25.24, U26.24
GP80_SD_0_DAT0: U2.66, U3.66
GP80_SD_0_DAT1: U4.66, U5.66
GP80_SD_0_DAT2: U7.66, U8.66
GP80_SD_0_DAT3: U10.66, U11.66
GP80_SD_0_DAT4: U13.66, U14.66
GP80_SD_0_DAT5: U16.66, U17.66
GP80_SD_0_DAT6: U19.66, U20.66
GP80_SD_0_DAT7: U22.66, U23.66
GP80_SD_0_DAT8: U25.66, U26.66
GP80_SD_0_DAT9: U28.66, U29.66
GP80_SD_0_DAT10: U31.66, U32.66
GP80_SD_0_DAT11: U34.66, U35.66
GP80_SD_0_DAT12: U37.66, U38.66
GP80_SD_0_DAT13: U40.66, U41.66
GP80_SD_0_DAT14: U43.66, U44.66
GP80_SD_0_DAT15: U46.66, U47.66
GP80_SD_0_DAT16: U49.66, U50.66
GP80_SD_0_DAT17: U52.66, U53.66
GP80_SD_0_DAT18: U55.66, U56.66
GP80_SD_0_DAT19: U58.66, U59.66
GP80_SD_0_DAT20: U61.66, U62.66
GP80_SD_0_DAT21: U64.66, U65.66
GP80_SD_0_DAT22: U67.66, U68.66
GP80_SD_0_DAT23: U70.66, U71.66
GP80_SD_0_DAT24: U73.66, U74.66
GP80_SD_0_DAT25: U76.66, U77.66
GP80_SD_0_DAT26: U79.66, U80.66
GP80_SD_0_DAT27: U82.66, U83.66
GP80_SD_0_DAT28: U85.66, U86.66
GP80_SD_0_DAT29: U88.66, U89.66
GP80_SD_0_DAT30: U91.66, U92.66
GP80_SD_0_DAT31: U94.66, U95.66
GP81: U28.48, U29.48
GP81_SD_0_DAT1: U2.70, U3.70
GP81_SD_0_DAT2: U4.70, U5.70
GP81_SD_0_DAT3: U7.70, U8.70
GP81_SD_0_DAT4: U10.70, U11.70
GP81_SD_0_DAT5: U13.70, U14.70
GP81_SD_0_DAT6: U16.70, U17.70
GP81_SD_0_DAT7: U19.70, U20.70
GP81_SD_0_DAT8: U22.70, U23.70
GP81_SD_0_DAT9: U25.70, U26.70
GP81_SD_0_DAT10: U28.70, U29.70
GP81_SD_0_DAT11: U31.70, U32.70
GP81_SD_0_DAT12: U34.70, U35.70
GP81_SD_0_DAT13: U37.70, U38.70
GP81_SD_0_DAT14: U40.70, U41.70
GP81_SD_0_DAT15: U43.70, U44.70
GP81_SD_0_DAT16: U46.70, U47.70
GP81_SD_0_DAT17: U49.70, U50.70
GP81_SD_0_DAT18: U52.70, U53.70
GP81_SD_0_DAT19: U55.70, U56.70
GP81_SD_0_DAT20: U58.70, U59.70
GP81_SD_0_DAT21: U61.70, U62.70
GP81_SD_0_DAT22: U64.70, U65.70
GP81_SD_0_DAT23: U67.70, U68.70
GP81_SD_0_DAT24: U70.70, U71.70
GP81_SD_0_DAT25: U73.70, U74.70
GP81_SD_0_DAT26: U76.70, U77.70
GP81_SD_0_DAT27: U79.70, U80.70
GP81_SD_0_DAT28: U82.70, U83.70
GP81_SD_0_DAT29: U85.70, U86.70
GP81_SD_0_DAT30: U88.70, U89.70
GP81_SD_0_DAT31: U91.70, U92.70
GP81_SD_0_DAT32: U94.70, U95.70
GP82: U28.42, U29.42
GP82_SD_0_DAT1: U4.64, U5.64
GP82_SD_0_DAT2: U2.64, U3.64
GP82_SD_0_DAT3: U7.64, U8.64
GP82_SD_0_DAT4: U10.64, U11.64
GP82_SD_0_DAT5: U13.64, U14.64
GP82_SD_0_DAT6: U16.64, U17.64
GP82_SD_0_DAT7: U19.64, U20.64
GP82_SD_0_DAT8: U22.64, U23.64
GP82_SD_0_DAT9: U25.64, U26.64
GP82_SD_0_DAT10: U28.64, U29.64
GP82_SD_0_DAT11: U31.64, U32.64
GP82_SD_0_DAT12: U34.64, U35.64
GP82_SD_0_DAT13: U37.64, U38.64
GP82_SD_0_DAT14: U40.64, U41.64
GP82_SD_0_DAT15: U43.64, U44.64
GP82_SD_0_DAT16: U46.64, U47.64
GP82_SD_0_DAT17: U49.64, U50.64
GP82_SD_0_DAT18: U52.64, U53.64
GP82_SD_0_DAT19: U55.64, U56.64
GP82_SD_0_DAT20: U58.64, U59.64
GP82_SD_0_DAT21: U61.64, U62.64
GP82_SD_0_DAT22: U64.64, U65.64
GP82_SD_0_DAT23: U67.64, U68.64
GP82_SD_0_DAT24: U70.64, U71.64
GP82_SD_0_DAT25: U73.64, U74.64
GP82_SD_0_DAT26: U76.64, U77.64
GP82_SD_0_DAT27: U79.64, U80.64
GP82_SD_0_DAT28: U82.64, U83.64
GP82_SD_0_DAT29: U85.64, U86.64
GP82_SD_0_DAT30: U88.64, U89.64
GP82_SD_0_DAT31: U91.64, U92.64
GP82_SD_0_DAT32: U94.64, U95.64
GP83: U28.34, U29.34
GP83_SD_0_DAT1: U4.68, U5.68
GP83_SD_0_DAT2: U7.68, U8.68
GP83_SD_0_DAT3: U2.68, U3.68
GP83_SD_0_DAT4: U10.68, U11.68
GP83_SD_0_DAT5: U13.68, U14.68
GP83_SD_0_DAT6: U16.68, U17.68
GP83_SD_0_DAT7: U19.68, U20.68
GP83_SD_0_DAT8: U22.68, U23.68
GP83_SD_0_DAT9: U25.68, U26.68
GP83_SD_0_DAT10: U28.68, U29.68
GP83_SD_0_DAT11: U31.68, U32.68
GP83_SD_0_DAT12: U34.68, U35.68
GP83_SD_0_DAT13: U37.68, U38.68
GP83_SD_0_DAT14: U40.68, U41.68
GP83_SD_0_DAT15: U43.68, U44.68
GP83_SD_0_DAT16: U46.68, U47.68
GP83_SD_0_DAT17: U49.68, U50.68
GP83_SD_0_DAT18: U52.68, U53.68
GP83_SD_0_DAT19: U55.68, U56.68
GP83_SD_0_DAT20: U58.68, U59.68
GP83_SD_0_DAT21: U61.68, U62.68
GP83_SD_0_DAT22: U64.68, U65.68
GP83_SD_0_DAT23: U67.68, U68.68
GP83_SD_0_DAT24: U70.68, U71.68
GP83_SD_0_DAT25: U73.68, U74.68
GP83_SD_0_DAT26: U76.68, U77.68
GP83_SD_0_DAT27: U79.68, U80.68
GP83_SD_0_DAT28: U82.68, U83.68
GP83_SD_0_DAT29: U85.68, U86.68
GP83_SD_0_DAT30: U88.68, U89.68
GP83_SD_0_DAT31: U91.68, U92.68
GP83_SD_0_DAT32: U94.68, U95.68
GP84: U28.32, U29.32
GP84_SD_CLK_FB: U2.44, U3.44
GP84_SD_CLK_FB1: U4.44, U5.44
GP84_SD_CLK_FB2: U7.44, U8.44
GP84_SD_CLK_FB3: U10.44, U11.44
GP84_SD_CLK_FB4: U13.44, U14.44
GP84_SD_CLK_FB5: U16.44, U17.44
GP84_SD_CLK_FB6: U19.44, U20.44
GP84_SD_CLK_FB7: U22.44, U23.44
GP84_SD_CLK_FB8: U25.44, U26.44
GP84_SD_CLK_FB9: U28.44, U29.44
GP84_SD_CLK_FB10: U31.44, U32.44
GP84_SD_CLK_FB11: U34.44, U35.44
GP84_SD_CLK_FB12: U37.44, U38.44
GP84_SD_CLK_FB13: U40.44, U41.44
GP84_SD_CLK_FB14: U43.44, U44.44
GP84_SD_CLK_FB15: U46.44, U47.44
GP84_SD_CLK_FB16: U49.44, U50.44
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
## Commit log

2014-08-09 Initial commit with templates
2014-08-09 layout ready for review. Renamed boards
2014-08-12 removed Edzzanine from name
2014-08-28 Updated Readme with small description
2014-09-20 corrected names, added DCIN, cleaned up dimensions
2014-09-20 added .epf ignore
2014-09-23 changed names of boards
2014-09-25 file cleanup
2014-10-16 Fix text rotation, go to v10
2014-10-17 Add some silk, update fp, ready for reds
2014-10-17 Ready for reds. Tweaked some silk positions, jumper position, on/off nomenclature No known to-do items
2014-10-21 created v10 panels
2015-10-01 Updating README with product links, documentation links
